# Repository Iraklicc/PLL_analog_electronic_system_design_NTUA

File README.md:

The final PLL in pcb form is at this path:
LABS/Lab8_Final/PLL_1

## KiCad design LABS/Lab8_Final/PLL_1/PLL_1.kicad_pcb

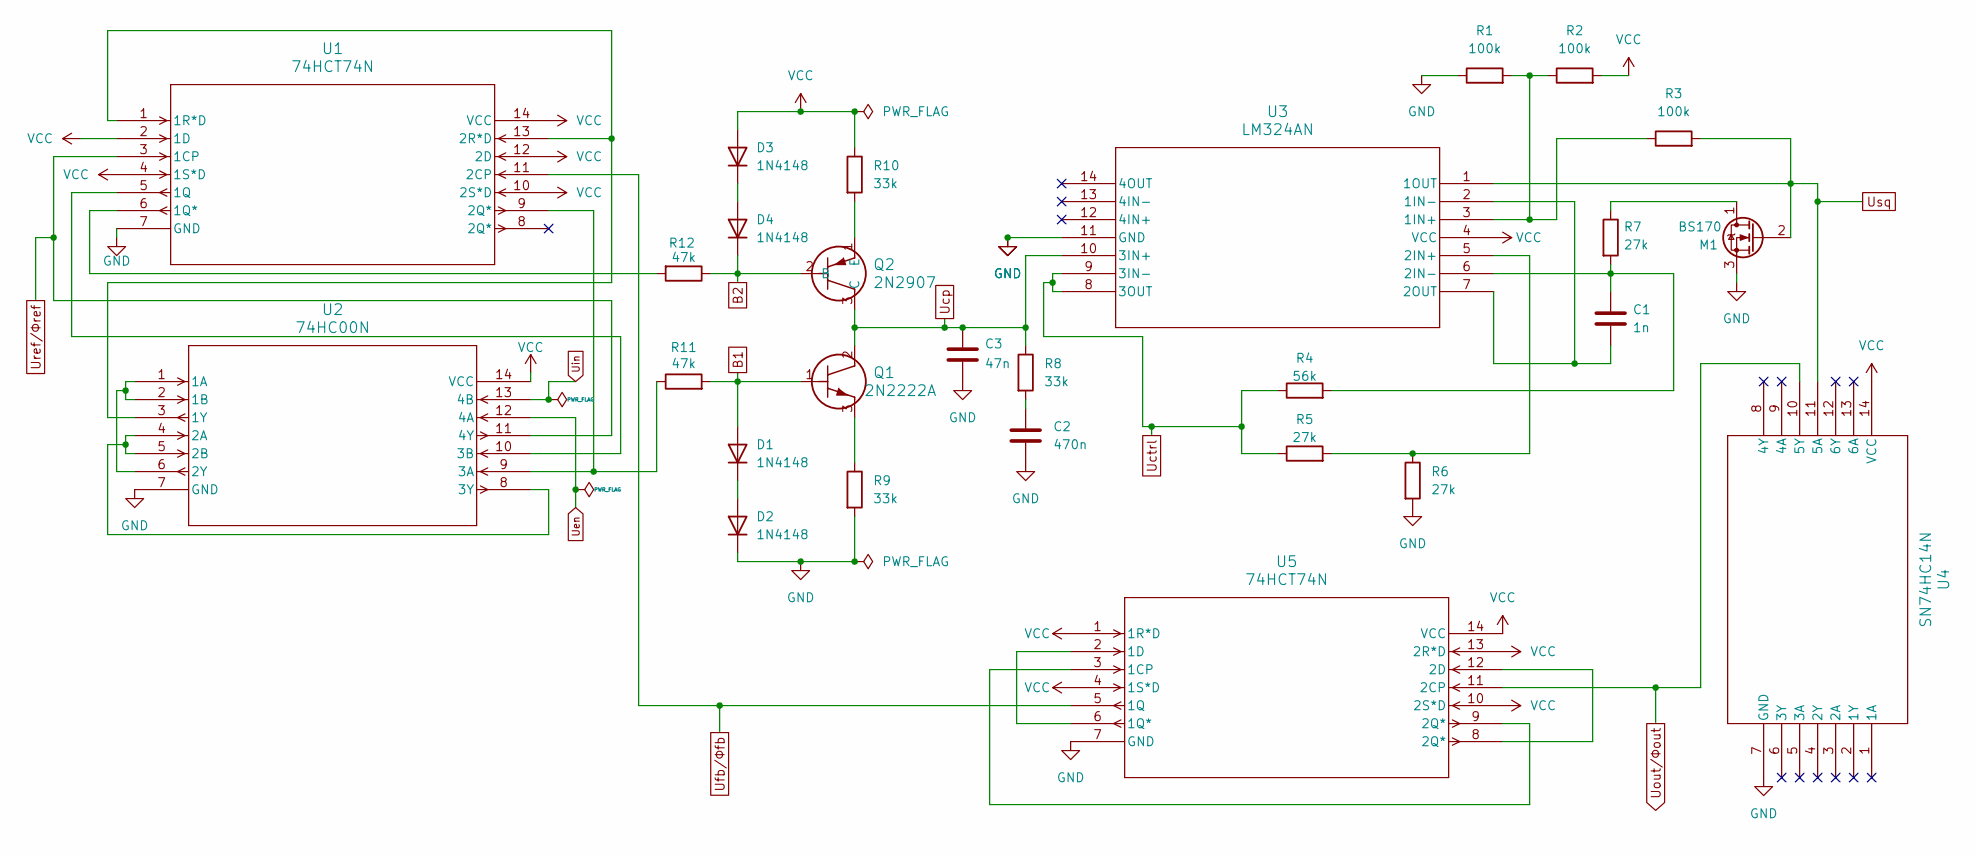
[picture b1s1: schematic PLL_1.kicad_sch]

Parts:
C1: 1n; C_Disc_D3.0mm_W1.6mm_P2.50mm
C2: 470n; C_Rect_L7.2mm_W2.5mm_P5.00mm_FKS2_FKP2_MKS2_MKP2
C3: 47n; C_Disc_D4.7mm_W2.5mm_P5.00mm
D1, D2, D3, D4: 1N4148; D_DO-35_SOD27_P7.62mm_Horizontal
Q1: 2N2222A; TO-18_STM
Q2: 2N2907; TO-18TO-206AA_MCH
R1, R2, R3: 100k; R_Axial_DIN0207_L6.3mm_D2.5mm_P7.62mm_Horizontal
R4: 56k; R_Axial_DIN0207_L6.3mm_D2.5mm_P7.62mm_Horizontal
R5, R6, R7: 27k; R_Axial_DIN0207_L6.3mm_D2.5mm_P7.62mm_Horizontal
R8, R9, R10: 33k; R_Axial_DIN0207_L6.3mm_D2.5mm_P7.62mm_Horizontal
R11, R12: 47k; R_Axial_DIN0207_L6.3mm_D2.5mm_P7.62mm_Horizontal
U1, U5: 74HCT74N; SOT27-1_NEX
U2: 74HC00N; SOT27-1_NEX (1)
U3: LM324AN; N14
U4: SN74HC14N; N14 (1)
Μ1: BS170; TO-92_Inline

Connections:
B1: D1.2 (A), Q1.1, R11.2
B2: D4.1 (K), Q2.2 (B), R12.1
GND: C2.2, C3.2, D2.1 (K), R1.1, R6.2, R9.2, U1.7 (GND), U2.7 (GND), U3.11 (GND), U4.7 (GND), U5.7 (GND), Μ1.3 (S)
unnamed: C2.1, R8.2
unnamed: D1.1 (K), D2.2 (A)
unnamed: D3.1 (K), D4.2 (A)
unnamed: Q1.3, R9.1
unnamed: Q2.1 (E), R10.2
unnamed: U1.5 (1Q), U2.10 (3B)
unnamed: R12.2, U1.6 (1Q*)
unnamed: U1.1 (1R*D), U1.13 (2R*D), U2.3 (1Y)
unnamed: U2.1 (1A), U2.2 (1B), U2.6 (2Y)
unnamed: U2.4 (2A), U2.5 (2B), U2.8 (3Y)
unnamed: R11.1, U1.9 (2Q*), U2.9 (3A)
unnamed: R1.2, R2.1, R3.1, U3.3 (1IN+)
unnamed: C1.1, U3.2 (1IN-), U3.7 (2OUT)
unnamed: R5.2, R6.1, U3.5 (2IN+)
unnamed: C1.2, R4.2, R7.2, U3.6 (2IN-)
unnamed: U5.3 (1CP), U5.9 (2Q*)
unnamed: U5.2 (1D), U5.6 (1Q*)
unnamed: U5.8 (2Q*), U5.12 (2D)
unnamed: R7.1, Μ1.1 (D)
Ucp: C3.1, Q1.2, Q2.3 (C), R8.1, U3.10 (3IN+)
Uctrl: R4.1, R5.1, U3.8 (3OUT), U3.9 (3IN-)
Uen: U2.12 (4A)
Ufb/Φfb: U1.11 (2CP), U5.5 (1Q)
Uin: U2.13 (4B)
Uout/Φout: U4.10 (5Y), U5.11 (2CP)
Uref/Φref: U1.3 (1CP), U2.11 (4Y)
Usq: R3.2, U3.1 (1OUT), U4.11 (5A), Μ1.2 (G)
VCC: D3.2 (A), R2.2, R10.1, U1.2 (1D), U1.4 (1S*D), U1.10 (2S*D), U1.12 (2D), U1.14 (VCC), U2.14 (VCC), U3.4 (VCC), U4.14 (VCC), U5.1 (1R*D), U5.4 (1S*D), U5.10 (2S*D), U5.13 (2R*D), U5.14 (VCC)

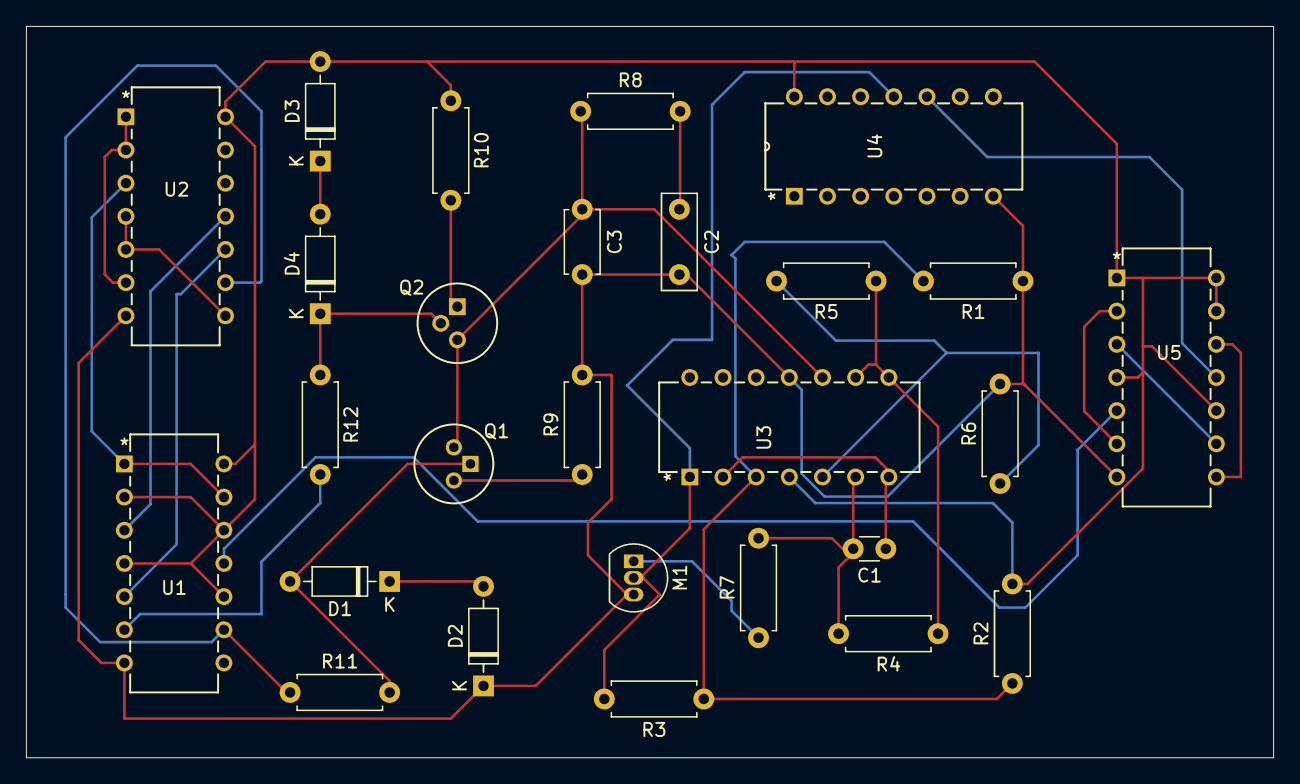
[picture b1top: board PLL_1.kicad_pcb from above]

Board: 2 copper layers, 95.5 x 56.0 mm, 27 parts (0 on the bottom side), 29 nets.
